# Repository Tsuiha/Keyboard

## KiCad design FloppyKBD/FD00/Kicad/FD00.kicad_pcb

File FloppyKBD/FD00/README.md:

# Keyboard

refer to https://tsuiha.com/floppykbd_00/

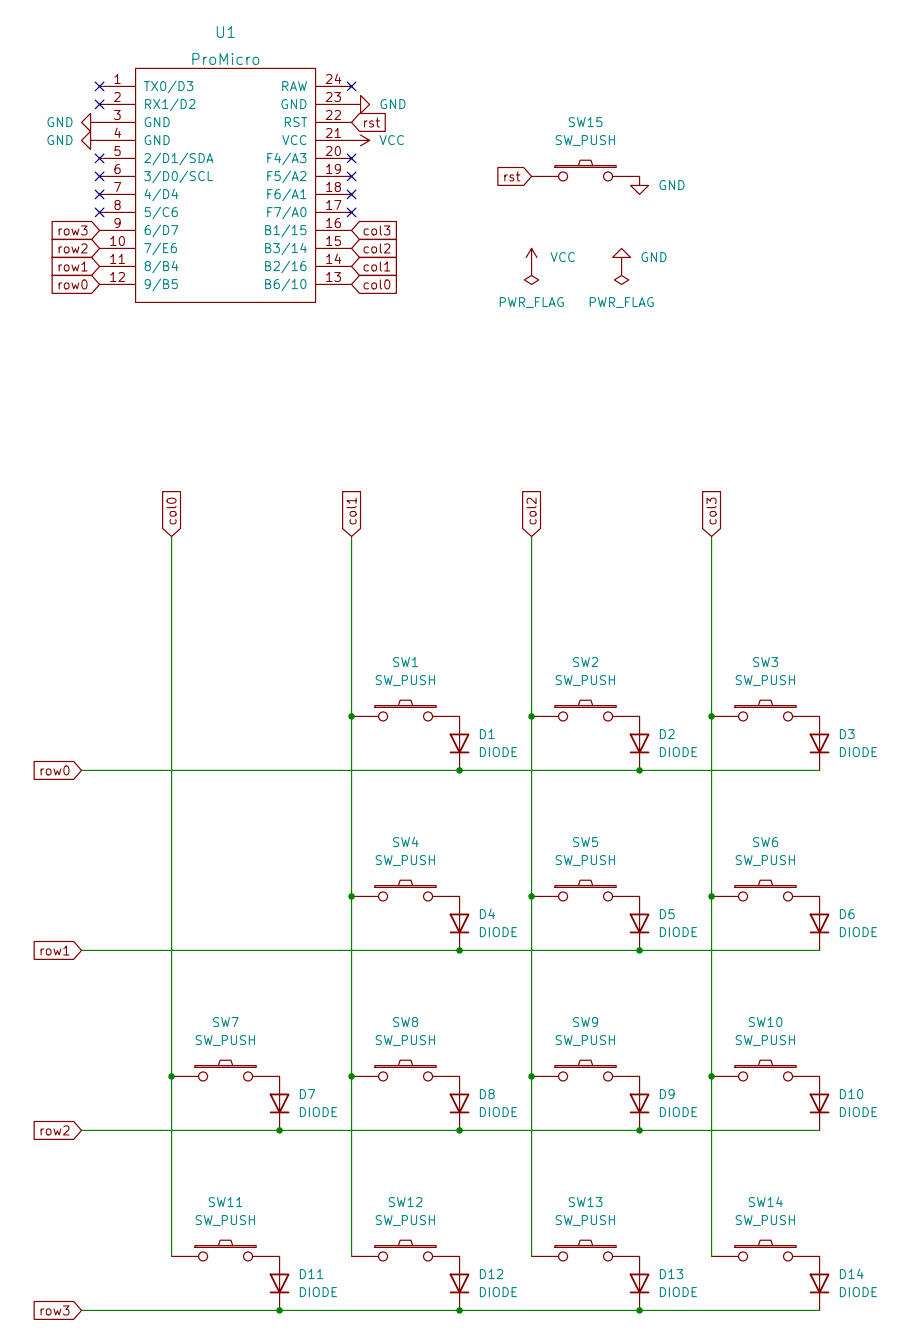
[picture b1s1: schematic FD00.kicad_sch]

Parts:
D1, D2, D3, D4, D5, D6, D7, D8, D9, D10, D11, D12, D13: DIODE; D3_SMD
D14: DIODE; D3_SMD_v2
SW1, SW2, SW3, SW4, SW5, SW6, SW7, SW8, SW9, SW10, SW11, SW12, SW13, SW14: SW_PUSH; CherryMX_Hotswap
SW15: SW_PUSH; ResetSW
U1: ProMicro; ArduinoProMicro

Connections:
GND: SW15.2, U1.3 (GND), U1.4 (GND), U1.23 (GND)
unnamed: D1.1 (A), SW1.2
unnamed: D2.1 (A), SW2.2
unnamed: D3.1 (A), SW3.2
unnamed: D4.1 (A), SW4.2
unnamed: D5.1 (A), SW5.2
unnamed: D6.1 (A), SW6.2
unnamed: D7.1 (A), SW7.2
unnamed: D8.1 (A), SW8.2
unnamed: D9.1 (A), SW9.2
unnamed: D10.1 (A), SW10.2
unnamed: D11.1 (A), SW11.2
unnamed: D12.1 (A), SW12.2
unnamed: D13.1 (A), SW13.2
unnamed: D14.1 (A), SW14.2
VCC: U1.21 (VCC)
col0: SW7.1, SW11.1, U1.13 (B6/10)
col1: SW1.1, SW4.1, SW8.1, SW12.1, U1.14 (B2/16)
col2: SW2.1, SW5.1, SW9.1, SW13.1, U1.15 (B3/14)
col3: SW3.1, SW6.1, SW10.1, SW14.1, U1.16 (B1/15)
row0: D1.2 (K), D2.2 (K), D3.2 (K), U1.12 (9/B5)
row1: D4.2 (K), D5.2 (K), D6.2 (K), U1.11 (8/B4)
row2: D7.2 (K), D8.2 (K), D9.2 (K), D10.2 (K), U1.10 (7/E6)
row3: D11.2 (K), D12.2 (K), D13.2 (K), D14.2 (K), U1.9 (6/D7)
rst: SW15.1, U1.22 (RST)

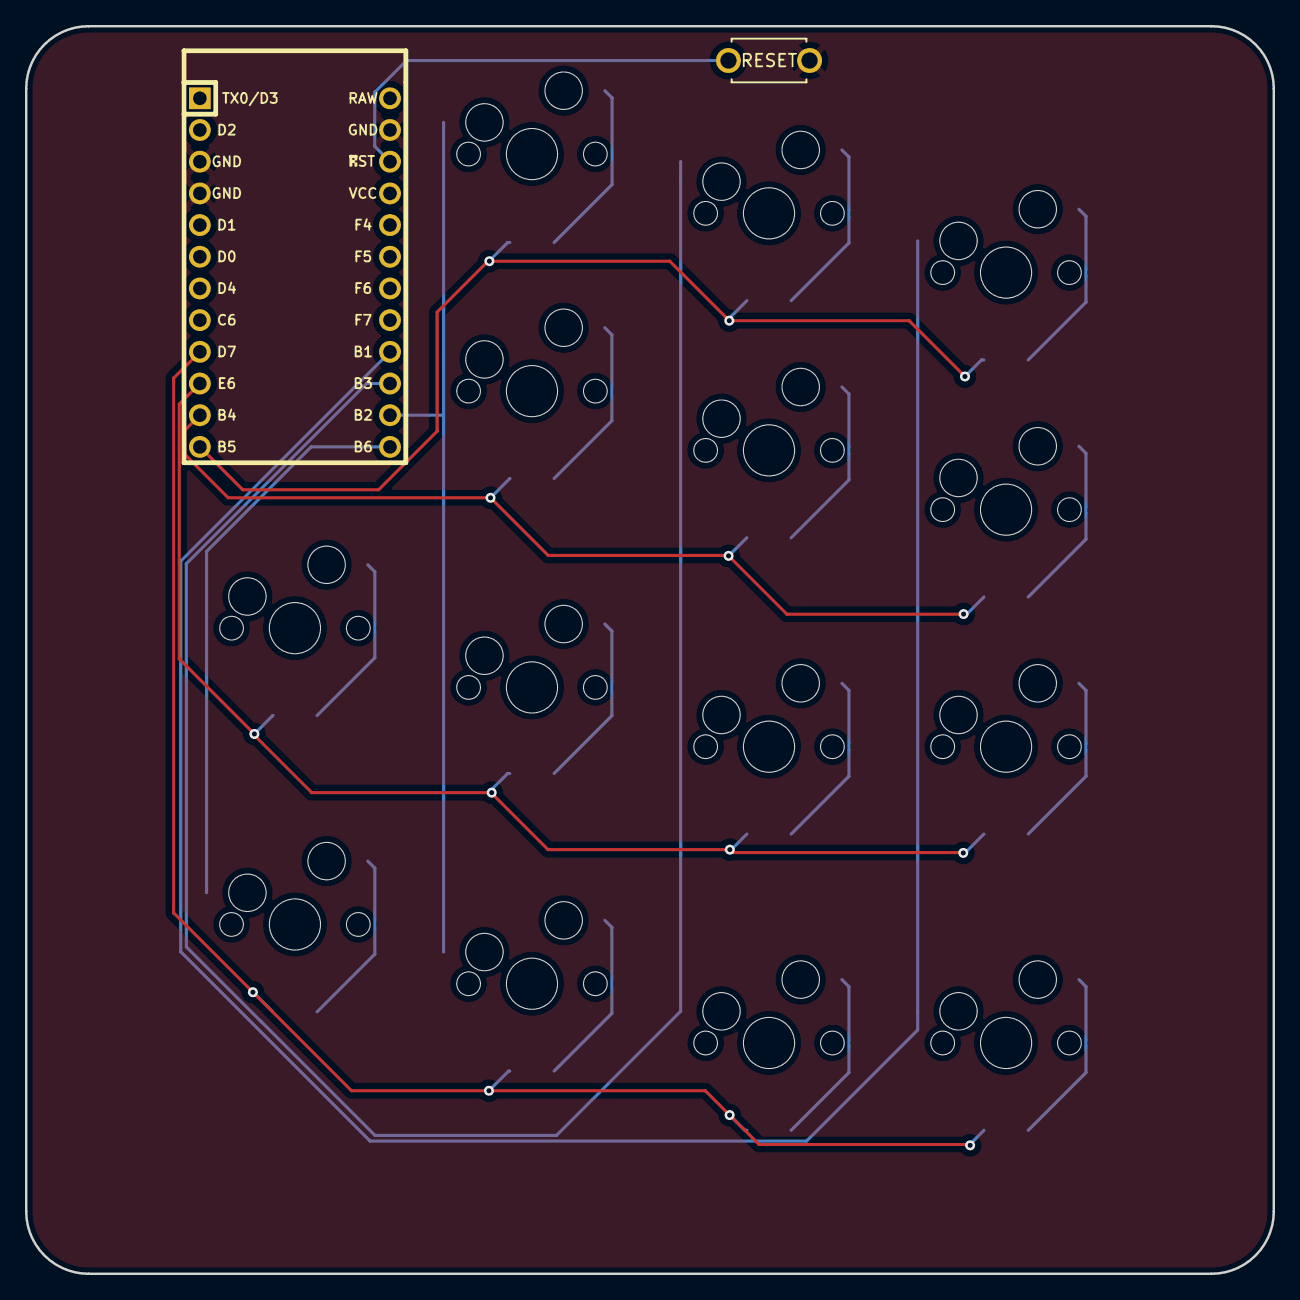
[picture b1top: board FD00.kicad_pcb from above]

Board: 2 copper layers, 100.0 x 100.0 mm, 30 parts (0 on the bottom side), 24 nets.

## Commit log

2022-09-05 wewew
2022-09-05 firstcommit
2022-09-06 grkeagjriea
2022-09-11 initial project version
2022-12-20 fcs42s
